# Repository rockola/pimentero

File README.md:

# pimentero

Echoplex preamp SMD PCB

PCB available on [OSH Park](https://oshpark.com/shared_projects/3f7JKBeo) - 3 PCBs for $1.80 shipped (Dec 2020)

* v0.1: initial import, unverified
* v0.2: added optional volume pot, verified

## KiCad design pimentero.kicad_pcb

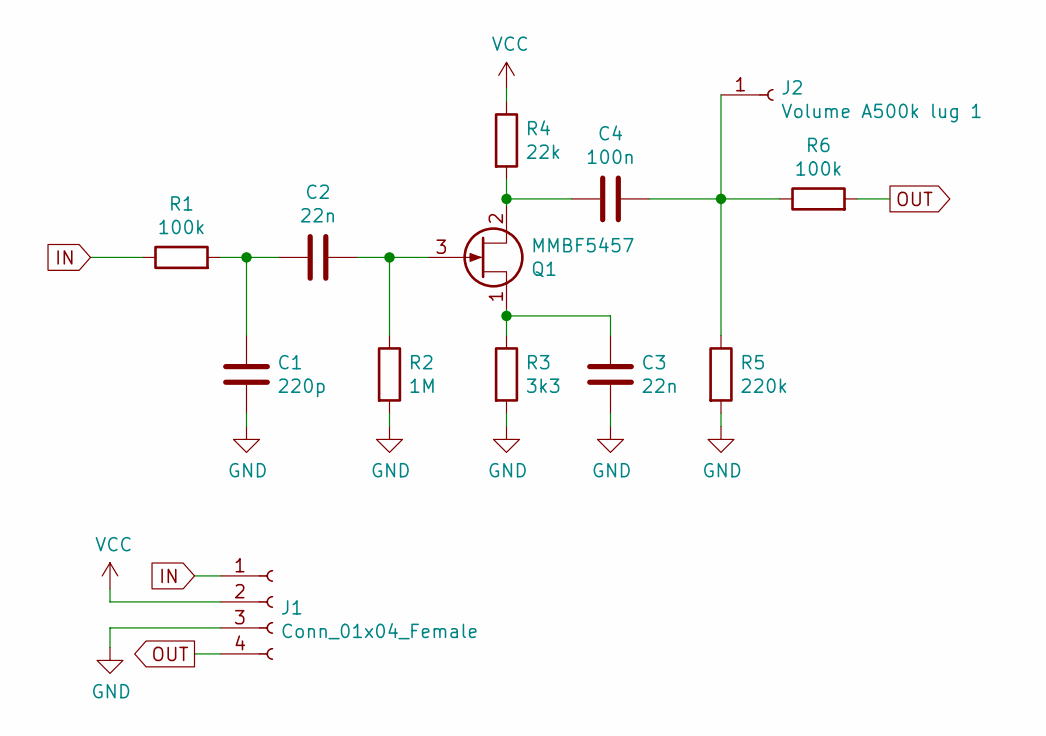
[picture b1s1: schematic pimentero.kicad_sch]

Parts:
C1: 220p; C_0805_2012Metric_Pad1.15x1.40mm_HandSolder
C2, C3: 22n; C_0805_2012Metric_Pad1.15x1.40mm_HandSolder
C4: 100n; C_0805_2012Metric_Pad1.15x1.40mm_HandSolder
J1: Conn_01x04_Female; PinHeader_1x04_P2.54mm_Vertical
J2: Volume A500k lug 1; PinHeader_1x01_P2.54mm_Vertical
Q1: MMBF5457; SOT-23
R1, R6: 100k; R_0805_2012Metric_Pad1.15x1.40mm_HandSolder
R2: 1M; R_0805_2012Metric_Pad1.15x1.40mm_HandSolder
R3: 3k3; R_0805_2012Metric_Pad1.15x1.40mm_HandSolder
R4: 22k; R_0805_2012Metric_Pad1.15x1.40mm_HandSolder
R5: 220k; R_0805_2012Metric_Pad1.15x1.40mm_HandSolder

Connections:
GND: C1.2, C3.2, J1.3, R2.2, R3.2, R5.2
IN: J1.1, R1.1
unnamed: C1.1, C2.1, R1.2
unnamed: C2.2, Q1.3 (G), R2.1
unnamed: C3.1, Q1.1 (D), R3.1
unnamed: C4.1, Q1.2 (S), R4.2
unnamed: C4.2, J2.1, R5.1, R6.1
OUT: J1.4, R6.2
VCC: J1.2, R4.1

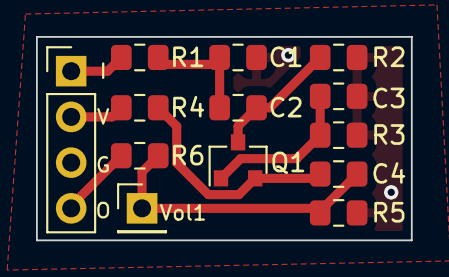
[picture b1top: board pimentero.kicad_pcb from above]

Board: 2 copper layers, 20.8 x 11.3 mm, 13 parts (0 on the bottom side), 9 nets.

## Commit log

2020-08-26 initial
2020-08-26 initial README
2020-08-26 v0.1 PCB and schematic
2020-08-26 v0.2: added volume pot (only pad for lug 1; lug 2 = GND, lug 3 = NC)
2020-08-26 v0.2 images with added vol pot lug
2020-08-26 note about v0.2, fixed image preview URLs
2020-11-23 Verification build was a resounding success
2020-12-09 Added Oshpark shared project link
2020-12-09 Markdown link bugfix
2022-01-11 updated to KiCad 6.0
